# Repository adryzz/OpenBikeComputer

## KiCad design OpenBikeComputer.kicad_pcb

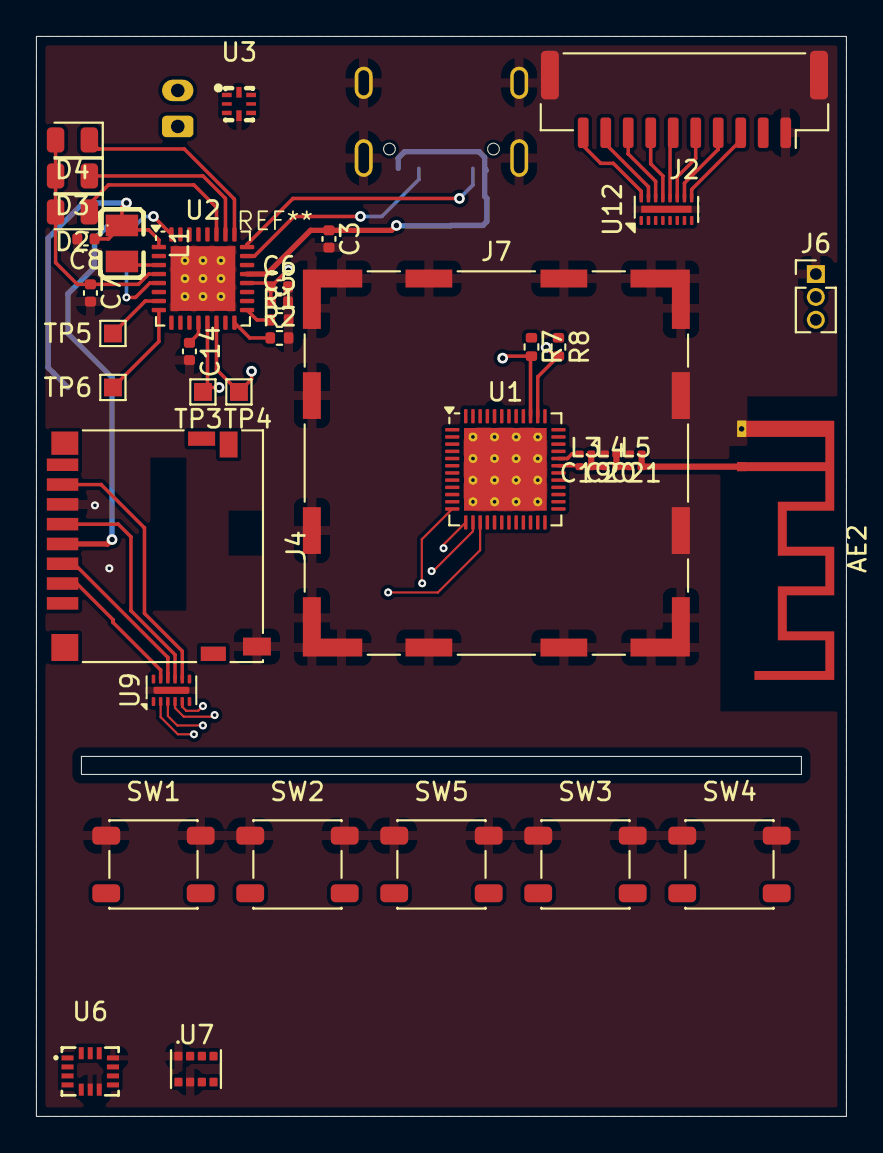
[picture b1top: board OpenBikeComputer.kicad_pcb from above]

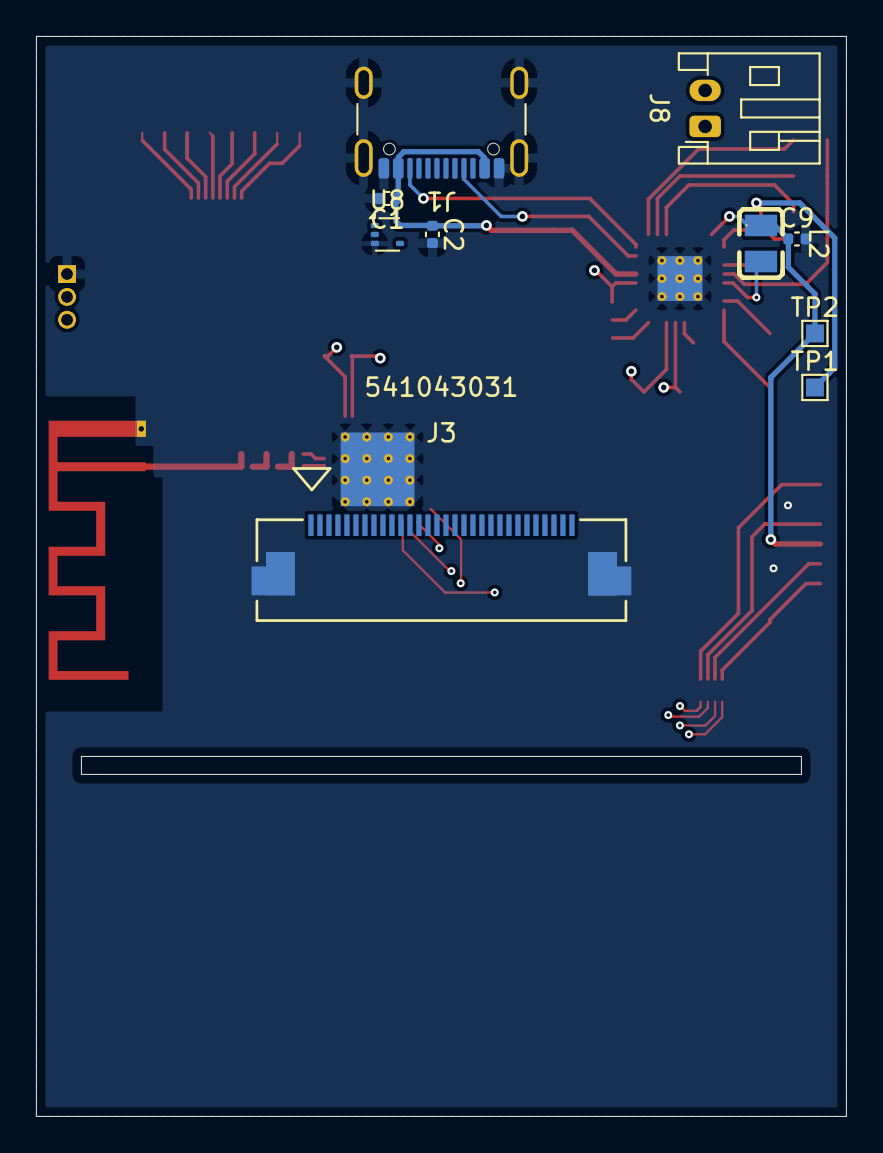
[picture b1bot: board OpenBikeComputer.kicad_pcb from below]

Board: 4 copper layers, 45.0 x 60.0 mm, 51 parts (10 on the bottom side), 59 nets.

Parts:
AE2: Antenna_Shield; Texas_SWRA117D_2.4GHz_Right
C1: 0.1pF; C_0402_1005Metric
C2, C14: 100nF; C_0402_1005Metric
C3: 1.0uF; C_0402_1005Metric
C5, C6, C7, C8, C9: 10uF; C_0402_1005Metric
C19: 1.5pF; C_0201_0603Metric
C20: 2.0pF; C_0201_0603Metric
C21: 0.3pF; C_0201_0603Metric
D2: R; LED_0805_2012Metric
D3: G; LED_0805_2012Metric
D4: B; LED_0805_2012Metric
J1: USB_C_Receptacle_USB2.0_14P; USB_C_Receptacle_GCT_USB4105-xx-A_16P_TopMnt_Horizontal
J2: Conn_01x10; JST_GH_SM10B-GHS-TB_1x10-1MP_P1.25mm_Horizontal
J3: Conn_01x30_Socket; CON_541043031_MOL
J4: Micro_SD_Card_Det1; microSD_HC_Hirose_DM3D-SF
J6: Conn_01x03_Pin; PinHeader_1x03_P1.27mm_Vertical
J7: RFShield_TwoPieces; Wuerth_36103205_20x20mm
J8: Conn_01x02_Socket; JST_PH_S2B-PH-K_1x02_P2.00mm_Horizontal
L1, L2: 2.2uH; L0806
L3: 2.7nH; L_0201_0603Metric
L4, L5: 3.5nH; L_0201_0603Metric
R1: 4.7k; R_0402_1005Metric
R2: 150k; R_0402_1005Metric
R7, R8: 10k; R_0402_1005Metric
SW1, SW2, SW3, SW4, SW5: SW_Push; SW_SPST_PTS647_Sx50
TP1, TP2, TP3, TP4, TP5, TP6: TestPoint; TestPoint_Pad_1.0x1.0mm
U1: nRF54L15-QFXX; QFN-48-1EP_6x6mm_P0.4mm_EP4.6x4.6mm_ThermalVias
U2: nPM1300-QEXX; QFN-32-1EP_5x5mm_P0.5mm_EP3.6x3.6mm_ThermalVias
U3: BQ298012RUGR; X2QFN-8_L1.5-W1.5-P0.50-TL
U6: ICM-42688-P; LGA-14_L3.0-W2.5-P0.50-TL
U7: ICP-10111; PSON65P250X200X100-8N
U8: TPD3E001DRLR; SOT-553
U9: TPD6F003; Texas_R-PWSON-N12_EP0.4x2mm
U12: TPD8F003; WSON-16_3.3x1.35_P0.4mm

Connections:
+1V8: C8.1, C14.1, L1.1, R7.1, R8.1, TP1.1, U1.10 (VDD), U1.22 (VDD), U1.36 (VDD), U1.47 (VDD), U1.48 (VDD), U2.1 (VOUT1), U2.12 (VDDIO), U6.5 (VDDIO), U6.8 (VDD), U7.8 (VDD)
+3V0: C9.1, J2.2, J4.4 (VDD), L2.1, TP2.1, U2.32 (VOUT2)
/MCU/INT: TP6.1, U1.42 (P1.14), U2.8 (GPIO1)
/MCU/MOTION_INT: U1.18 (P2.07), U6.4 (INT1/INT)
/MCU/RESET: TP5.1, U1.41 (P1.13), U2.7 (GPIO0)
BATGND: J8.1, U3.3 (VSS)
BUT1: SW1.2, U1.23 (P0.00)
BUT2: SW2.2, U1.24 (P0.01)
BUT3: SW3.2, U1.27 (P0.02)
BUT4: SW4.2, U1.21 (P2.10)
CC1: J1.A5 (CC1), U2.23 (CC1)
CC2: J1.B5 (CC2), U2.24 (CC2)
DETECT1: U1.37 (P1.09), U12.8 (Ch8_In)
DETECT2: U1.40 (P1.12), U12.7 (Ch7_In)
GND: AE2.2 (Shield), C1.2, C2.2, C3.2, C5.2, C6.2, C7.2, C8.2, C9.2, C14.2, C19.2, C20.2, C21.2, J1.A1 (GND), J1.A12 (GND), J1.B1 (GND), J1.B12 (GND), J1.S1 (SHIELD), J2.1, J2.MP, J3.MP, J4.6 (VSS), J4.10 (SHIELD), J6.1, J7.1 (Shield), R1.2, R2.2, SW1.1, SW2.1, SW3.1, SW4.1, SW5.1, U1.32 (VSS_PA), U1.44 (VSS), U1.49 (VSS), U2.2 (PVSS1), U2.6 (PVSS2), U2.33 (AVSS), U3.4 (CS), U6.6 (GND), U6.7 (RESV), U6.11 (RESV), U7.1 (GND), U7.7 (GND), U8.3, U9.13 (GND), U12.17 (GND)
GPIO1: U1.29 (P0.04), U12.2 (Ch2_In)
GPIO2: U1.28 (P0.03), U12.1 (Ch1_In)
unnamed: AE2.1 (A), C21.1, L5.2
unnamed: C19.1, L3.2, L4.1
unnamed: C20.1, L4.2, L5.1
unnamed: D2.1 (K), U2.27 (LED2)
unnamed: D3.1 (K), U2.26 (LED1)
unnamed: D4.1 (K), U2.25 (LED0)
unnamed: J2.3, U12.9 (Ch8_Out)
unnamed: J2.4, U12.10 (Ch7_Out)
unnamed: J2.5, U12.11 (Ch6_Out)
unnamed: J2.6, U12.12 (Ch5_Out)
unnamed: J2.7, U12.13 (Ch4_Out)
unnamed: J2.8, U12.14 (Ch3_Out)
unnamed: J2.9, U12.15 (Ch2_Out)
unnamed: J2.10, U12.16 (Ch1_Out)
unnamed: J4.5 (CLK), U9.10 (Ch3_Out)
unnamed: J4.3 (CMD), U9.9 (Ch4_Out)
unnamed: J4.7 (DAT0), U9.11 (Ch2_Out)
unnamed: J4.2 (DAT3/CD), U9.8 (Ch5_Out)
unnamed: J6.2, U1.26 (SWDCLK)
unnamed: J6.3, U1.25 (SWDIO)
unnamed: L3.1, U1.31 (ANT)
unnamed: U1.33 (DECRF), U1.43 (DECA)
unnamed: SW5.2, U2.15 (SHPHLD)
unnamed: L1.2, U2.3 (SW1)
unnamed: L2.2, U2.5 (SW2)
unnamed: R1.1, U2.17 (VSET1)
unnamed: R2.1, U2.16 (VSET2)
SCL1: R7.2, TP4.1, U1.39 (P1.11), U2.14 (SCL)
SCL2: U1.9 (P1.08), U6.13 (AP_SCL/AP_SCLK), U7.4 (SCL)
SDA1: R8.2, TP3.1, U1.38 (P1.10), U2.13 (SDA)
SDA2: U1.11 (P2.00), U6.14 (AP_SDA/AP_SDIO/AP_SDI), U7.3 (SDA)
SD_CS: U1.15 (P2.04), U9.5 (Ch5_In)
SD_DETECT: J4.9 (DET), U1.16 (P2.05)
SD_MISO: U1.13 (P2.02), U9.2 (Ch2_In)
SD_MOSI: U1.14 (P2.03), U9.4 (Ch4_In)
SD_SCLK: U1.12 (P2.01), U9.3 (Ch3_In)
SENSE1A: U1.5 (P1.04), U12.6 (Ch6_In)
SENSE1B: U1.6 (P1.05), U12.5 (Ch5_In)
SENSE2A: U1.7 (P1.06), U12.4 (Ch4_In)
SENSE2B: U1.8 (P1.07), U12.3 (Ch3_In)
VBUS: C1.1, C2.1, C3.1, J1.A4 (VBUS), J1.A9 (VBUS), J1.B4 (VBUS), J1.B9 (VBUS), U2.21 (VBUS), U8.5
VSYS: C5.1, C6.1, C7.1, D2.2 (A), D3.2 (A), D4.2 (A), U2.4 (PVDD), U2.20 (VSYS)

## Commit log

2024-10-30 add inductor and crystal
2024-10-31 fixup design pcb clearances
2024-10-31 add power button
2024-10-31 use separate i2c bus for PMIC
2025-01-22 switch out SoC, stuff is in the air
2025-01-22 re-integrate all components + add BT antenna
2025-01-24 improve design a lot
2025-01-24 finish oled driver circuit
2025-01-25 route SD card traces and antenna traces semi-properly
2025-01-25 tune RF keepout of coplanar wave guide with GND plane to 0.25mm for 50 ohm impedance matching
2025-01-25 route SWD lines
2025-01-25 mark NFC components as DNP for rev1
2025-01-25 add copper pour on all layers
2025-01-25 move BT antenna, cleanup keepout zones and transmission line
2025-01-25 fixup antenna trace stuff
2025-01-25 clarify and set up board stackup properly
2025-01-25 rfinish routing PMIC (pretty crap routing)
2025-01-26 shitty routing job for rev1
2025-01-26 change RF shield
2025-01-27 begin new board
2025-01-27 lay out components
2025-01-27 add lots of test points
2025-01-27 housekeeping
2025-01-28 route PMIC
2025-01-28 start routing MCU + switch out pin assignments
2025-01-28 sd card (todo see if we can use a better connector to avoid routing like this)
2025-01-28 add sd card model and stuff
2025-01-28 stuff
2025-01-30 quick
2025-01-30 power button
2025-01-31 add keepout around antenna transmission line
2025-02-02 replace RJ45 with JST GH connector, add 2 I2C capable GPIOs to output port
2025-02-02 rearrange output GPIO pin assignments to allow for more better things
2025-02-02 add TVS diodes on I/O port
2025-02-02 ground mounting pads for connectors
2025-02-02 fix various net issues
2025-02-02 lock a few footprints
2025-02-03 thicken I/O port traces
